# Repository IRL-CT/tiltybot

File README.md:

# TiltyBot

A smartphone-controlled robot platform built on the ESP32-S3 and Dynamixel XL330 servo motors. The robot hosts its own Wi-Fi network and serves a browser-based control interface — no app install required.

Building on Rei Lee's [ConeBot](https://github.com/rei039474/ConeBot).

## Guides

- **[TiltyBot Intro](TiltyBot_Intro_EN.md)** — connect and use
- **[TiltyBot Assembly & Advanced](TiltyBot_Advanced_EN.md)** — build, flash, modify

## What it does

Connect your phone to the robot's Wi-Fi, open `https://192.168.4.1`, and pick a mode:

- **Drive** — joystick differential drive
- **Tilty** — phone gyro pan/tilt (Android) or manual sliders
- **2-Motor** — direct position control
- **Puppet** — one robot mirrors another via ESP-NOW
- **Sound** — TTS, soundboard, recording
- **Calibrate** — set motor home position and limits

## Hardware

- [Waveshare ESP32-S3-Zero](https://www.waveshare.com/esp32-s3-zero.htm)
- 2× [Dynamixel XL330-M077-T](https://robotis.us/dynamixel-xl330-m077-t/)
- USB-C cable and power source

## Quick start

```bash
git clone https://github.com/imandel/tiltybot.git
cd tiltybot
pio run -e tiltybot -t upload
pio run -e tiltybot -t uploadfs
```

Connect your phone to the `BOT-*` Wi-Fi (password: `12345678`), open `https://192.168.4.1`.

## License

MIT

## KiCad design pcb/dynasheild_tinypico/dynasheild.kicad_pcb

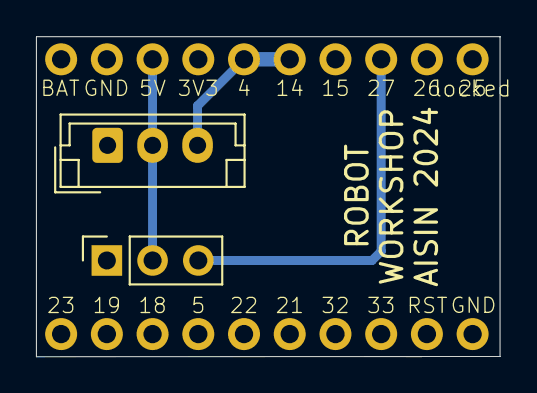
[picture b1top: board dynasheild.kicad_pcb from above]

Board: 2 copper layers, 25.8 x 17.8 mm, 4 parts (0 on the bottom side), 4 nets.

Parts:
J1: B3B-EH-ALFSN; JST_EH_B3B-EH-A_1x03_P2.50mm_Vertical
J2: Conn_01x03_Pin; PinSocket_1x03_P2.54mm_Vertical
LEFT0: TINYPICO_HEADER_10NO_SILK_PTH_FEMALE; 1X10_NO_SILK
RIGHT0: TINYPICO_HEADER_10NO_SILK_PTH_FEMALE; 1X10_NO_SILK

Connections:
/GND: J1.1, J2.1, LEFT0.2, RIGHT0.10
/GPIO14: J1.3, LEFT0.5, LEFT0.6
/GPIO27: J2.3, LEFT0.8
/USB: J1.2, J2.2, LEFT0.3

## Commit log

2026-02-23 docs
2026-02-27 hardware links
    Updated hardware list with links and additional items.
2026-03-20 feat: port to ESP32-S3-Zero with PsychicHttp
    - Replace TinyPICO/ESP32 with Waveshare ESP32-S3-Zero
    - Replace ESP32_HTTPS_Server with PsychicHttp (ESP-IDF native)
    - Use pioarduino platform for ESP-IDF 5.x / Arduino Core 3.x
    - Custom partition table for 4MB flash (1.75MB app + 2.19MB LittleFS)
    - Self-signed EC cert for HTTPS
    - Each mode (drive, tilty, 2motor) is a separate PIO environment
2026-03-20 feat: unified firmware with all three modes
    - Single firmware serves drive, tilty, and 2-motor modes
    - Index page at / with links to each mode
    - Each mode has its own WebSocket endpoint (/ws/drive, /ws/tilty, /ws/2motor)
    - Motor control mode switches automatically when client connects
    - Drive mode stops motors on WebSocket disconnect
    - All HTML inlined in firmware (no LittleFS needed for UI)
2026-03-20 refactor: clean up project structure
    - Rename src/drive/ to src/tiltybot/ to match env name
    - Remove old HTML/JS/CSS data files (UI is now inlined in firmware)
    - Keep only SSL certs in data/
    - Move motor commands to main loop for thread safety
    - Update comment header with correct flash command
    - LittleFS only used for SSL certificates
2026-03-20 docs: update README for ESP32-S3-Zero + PsychicHttp
    - Replace TinyPICO references with Waveshare ESP32-S3-Zero
    - Document wiring (GPIO1+GPIO2 for Dynamixel data)
    - Add motor setup instructions
    - Document unified firmware with all modes
    - Update project structure and PIO environments
    - Add SSL cert regeneration instructions
2026-03-20 docs: update workshop guide for ESP32-S3-Zero
    - Rewrite EN guide for new hardware and unified firmware
    - Remove TinyPICO-specific instructions
    - Add motor setup tool instructions
    - Simplify mode selection (index page instead of platformio.ini)
    - Add TODO markers for screenshots that need updating
    - Mark JP guide as needing translation update
2026-03-21 feat: add HTTP->HTTPS redirect on port 80
    - Run second HTTP server on port 80 that redirects all requests to HTTPS
    - Users can type http://192.168.4.1 and get redirected automatically
    - Fixes Android Chrome defaulting to http:// when no protocol specified
2026-03-21 docs: add TODO list
2026-03-21 feat: add sound recorder page
    - Inline sound recorder HTML/JS in firmware
    - Restyled to match dark theme
    - Accessible from index page
    - Records audio via phone mic, plays back through phone/BT speaker
    - Purely client-side, no motor interaction
    - Removed old LittleFS sound files
2026-03-21 chore: add blank KiCad project for ESP32-S3-Zero dynashield
    - Blank schematic, PCB, and project files for KiCad 8
    - README with wiring table and SnapEDA part import instructions
    - ESP32-S3-Zero mounts underneath via castellated holes
    - B3B-EH-ALFSN connector for Dynamixel XL330
2026-04-03 feat(sound): add file upload, trim controls, fix metadata race condition
2026-04-03 refactor: move all HTML pages from PROGMEM to LittleFS
2026-04-07 feat: add puppet mode, tilty smoothing, calibration test, no-cache headers
    - Puppet mode: ESP-NOW based robot-to-robot mirroring with emoji pairing
    - Tilty: low-pass filter, gimbal lock protection, 30Hz throttle, float pan mapping
    - Calibration test: standalone tool for homing offset and position limits
    - Serve HTML with no-cache headers to prevent stale pages
    - Use XL330 fork with setHomingOffset/setMinPositionLimit/setMaxPositionLimit
    - Conditional serial logging (only when monitor connected)
2026-04-07 chore: remove calibration test (debugging tool, no longer needed)
2026-04-07 chore: point XL330 library back to upstream (PR merged)
2026-04-07 feat(tilty): replace Euler angles with RelativeOrientationSensor quaternions
    - Use Android RelativeOrientationSensor for hardware quaternion input
    - Delta quaternion from reference pose with YXZ Euler decomposition
    - Eliminates gimbal lock (singularity moved to tilt=±90°, unreachable)
    - Tilt/pan crosstalk reduced to ~18° (from 100°+ jumps)
    - Add calibration page with homing offset and position limit controls
    - Add analysis/plotting scripts for tilty logs
2026-04-08 fix(puppet): ESP-NOW interface, motor reads, degree-based packets
    - Fix ESP_ERR_ESPNOW_IF: set peer.ifidx = WIFI_IF_AP for AP-only mode
    - Fix controller motor reads: use readMotorPosition() (echo-skip)
    - Send degrees instead of raw positions so each robot uses own calibration
    - Add BOT_SSID build flag for compile-time SSID configuration
    - Add puppet debug logging (throttled)
    - Update README with puppet, calibration, tilty gyro docs
2026-04-08 chore: remove debug UI from tilty page
2026-04-08 docs: remove pre-assembly zeroing instructions (calibration replaces it)
2026-04-08 fix(puppet): stop puppet mode when entering any other mode
2026-04-08 fix(calibrate): slow down test sequence, add tilt direction note
2026-04-08 fix(calibrate): use profile velocity for slower test movements
2026-04-08 fix(tilty): negate tilt for reversed motor installation
2026-04-08 feat(puppet): add EMA smoothing for puppet following
    Puppet motor updates run at ~100Hz with EMA (alpha=0.2) to smooth
    received positions. Eliminates jerk when controller stops after fast
    movement. No deadband — every position change writes to motor.
2026-04-08 fix(tilty): raise tilt limit to 80 deg (measured physical clearance is 93 deg)
2026-04-08 chore: remove debug logs, analysis scripts, boilerplate files
2026-04-08 feat(sound): add text-to-speech with saved phrase buttons
    Uses Web Speech API (works offline). Type text and press Enter or
    Speak button. Save button creates reusable phrase buttons. Phrases
    persist in localStorage. Voice selector for available system voices.
2026-04-08 refactor(ui): shared CSS, consistent design, sound page rewrite
    Extract common styles into data/style.css, linked from all pages.
    Unified color palette, remove emojis from chrome, flat dark theme.
    Sound page rewritten: TTS with saved phrases, synthesized soundboard
    with saveable sounds, recording with save/discard, file upload.
    Audio clips stored in IndexedDB. Saved section always visible at top.
    Add /style.css route to firmware.
2026-04-08 fix(drive): sync write, watchdog, reliable stop
    - Sync Write (Dynamixel 0x83) sends both motor PWM values in one
    packet so motors start/stop simultaneously with zero inter-motor delay
    - Drive watchdog stops motors after 300ms with no client frames
    - Always write both motors on every 10Hz heartbeat frame so stop
    commands are never lost to a single dropped bus packet
    - Transition logging: moving/stopped state changes, zero write count,
2026-04-15 docs(workshop): split intro/advanced and move media to assets
    - Add TiltyBot_Intro_EN.md with browser-first workshop flow
    - Add TiltyBot_Advanced_EN.md for technical setup/debug details
    - Move legacy EN/JP workshop guides into assets/ to keep root clean
    - Rename img/ -> assets/ and update markdown image paths
    - Add new phone screenshots and robot photo used in Intro
    - Keep demo GIFs (ConeBot, drive, tilty) in relevant sections
2026-04-15 docs: simplify README, consolidate guides
    - README trimmed to overview + GIFs + links to guides
    - Intro: phone screenshots at width=320, link renamed
    - Advanced: renamed to Assembly & Advanced, absorbed hardware/
    wiring/motor setup/CLI reference from README
2026-04-20 updated lab
2026-04-20 minor edits
2026-04-20 Rename TiltyBot_Lab_EN.md to index.md
